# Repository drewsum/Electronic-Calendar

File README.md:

# Electronic-Calendar
Small PCB to show Time, Date, and Day of the Week. Centered around a PIC32MZ

Hardware:
KiCad Project for single PCB is located in hdw/KiCad_Project
Built in KiCad 5.1.0
Requires drewsum's custom libraries for KiCad schematic symbols and PCB footprints, located at: https://github.com/drewsum/KiCad_Custom_Libraries.git

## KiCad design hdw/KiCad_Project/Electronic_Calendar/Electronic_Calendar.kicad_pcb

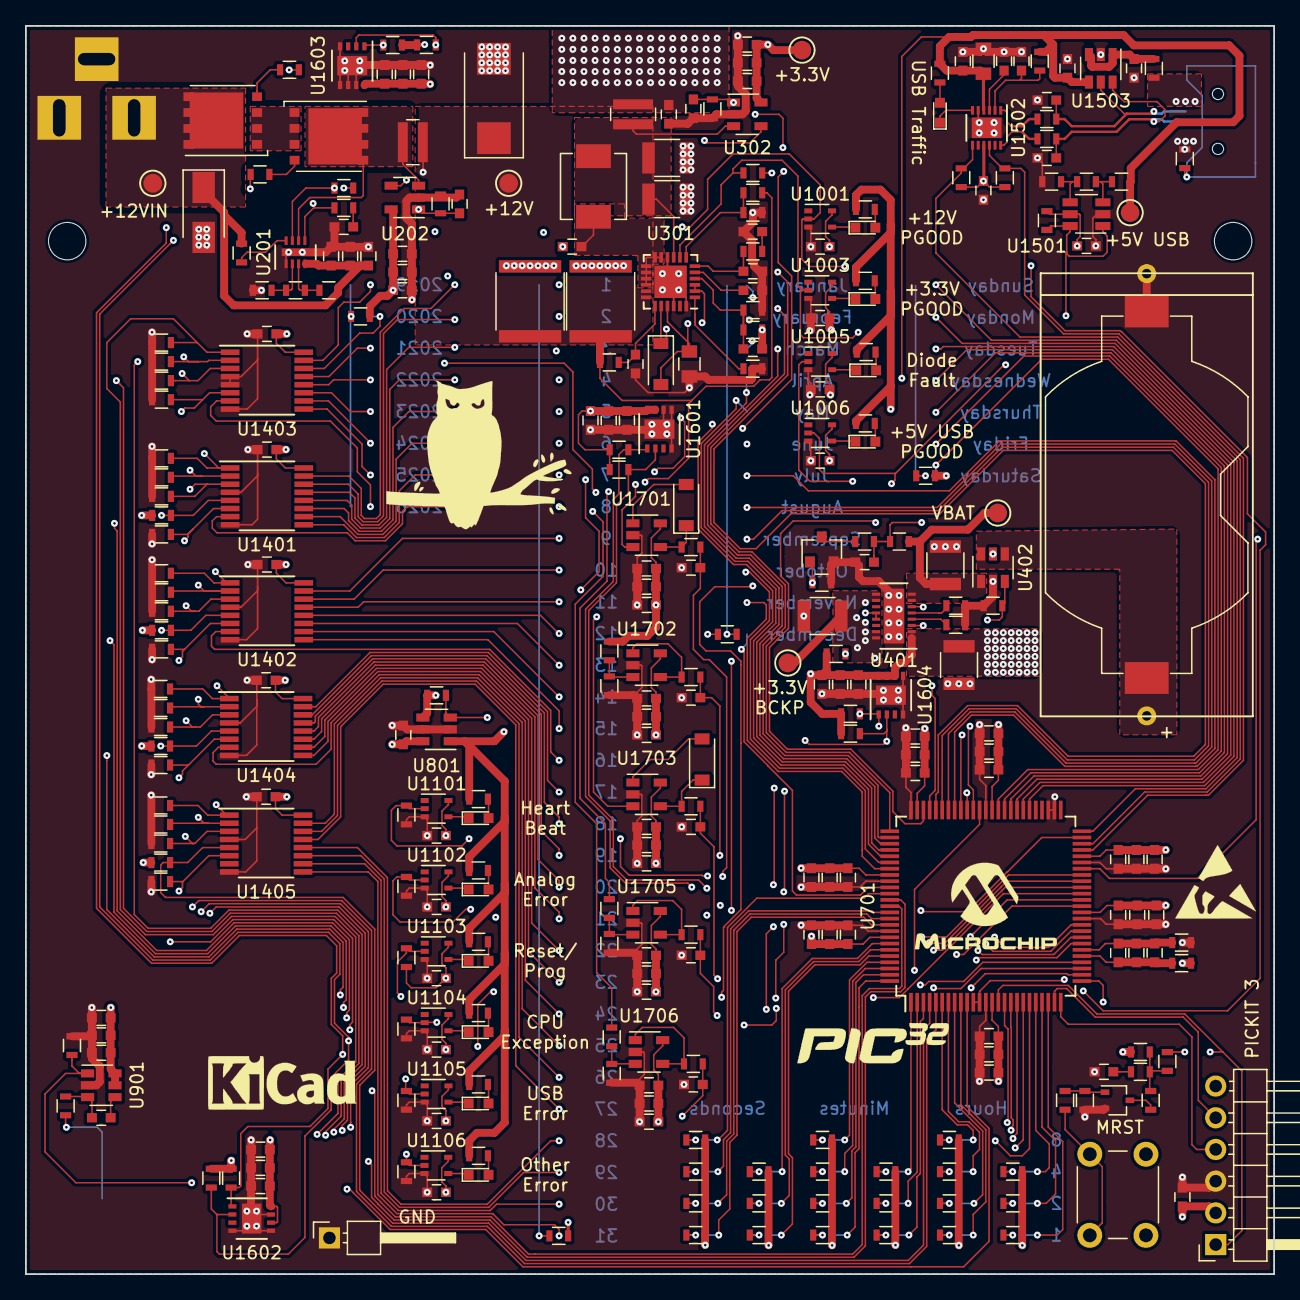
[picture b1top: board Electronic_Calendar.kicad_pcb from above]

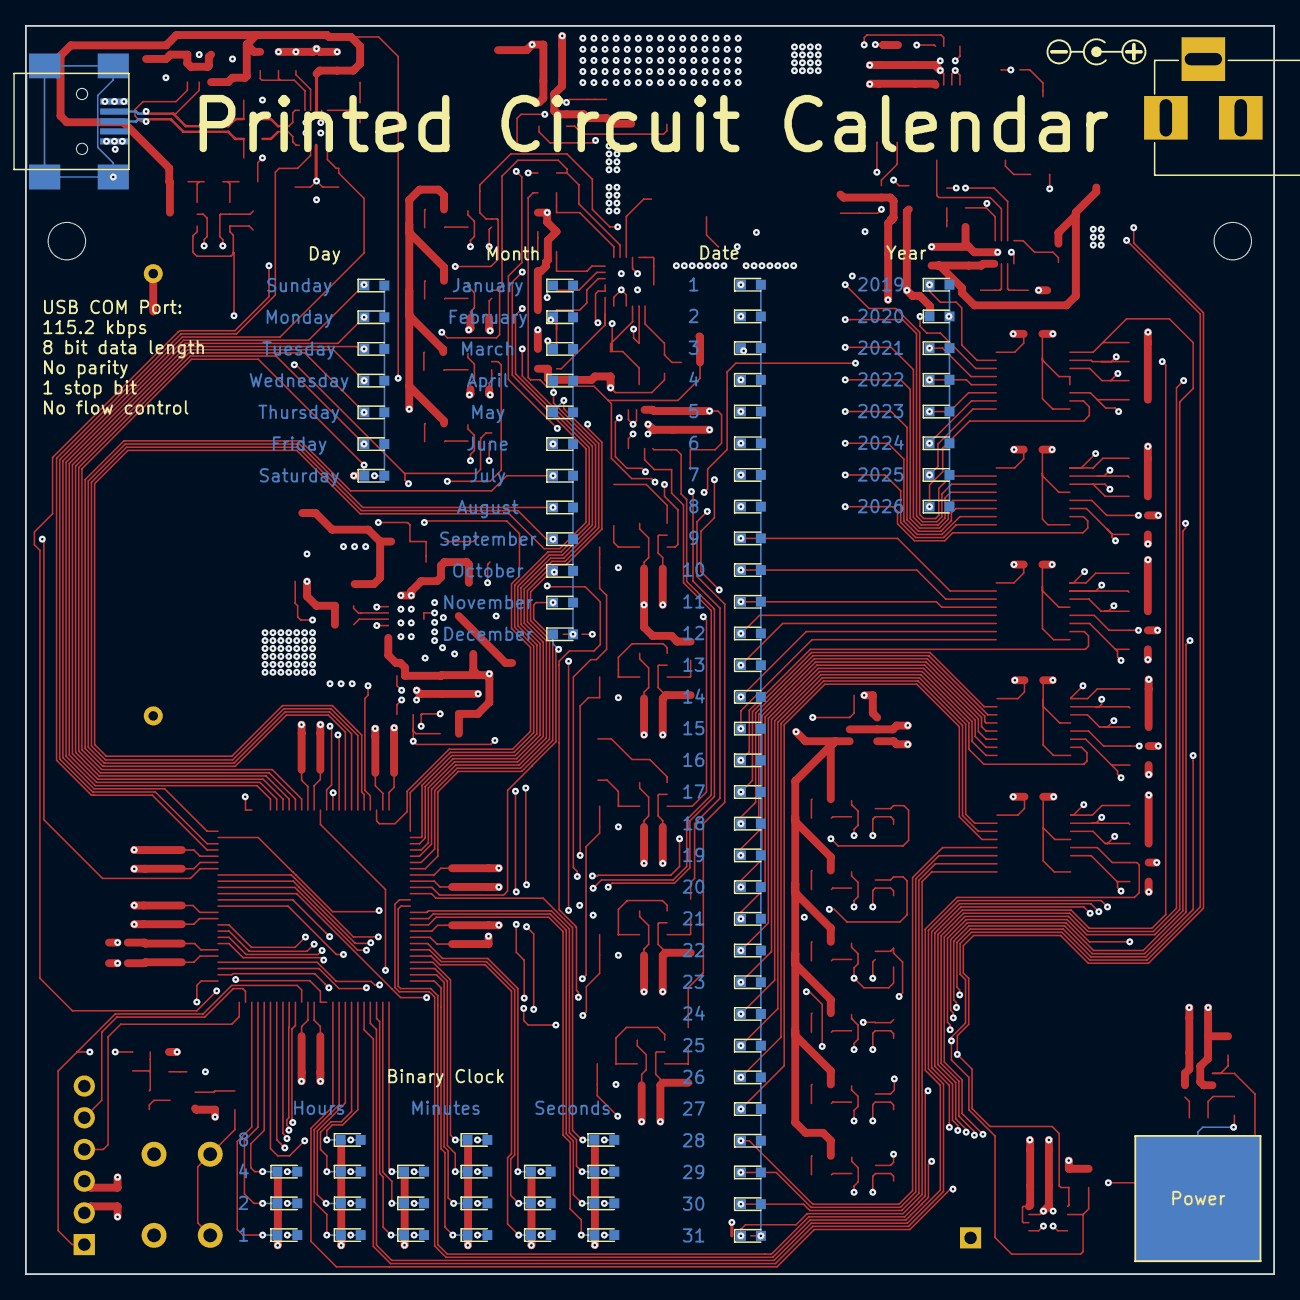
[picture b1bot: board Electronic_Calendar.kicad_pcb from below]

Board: 4 copper layers, 100.0 x 100.0 mm, 399 parts (82 on the bottom side), 229 nets.

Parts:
BT401: BR-2/3AE5SPN; BR-2_3AE5SPN
C201, C204, C205, C305, C307, C311, C316, C401, C601, C602, C801, C802, C807, C808, C813, C814, C819, C820, C825, C902, C1001, C1003, C1005, C1006, C1101, C1102, C1103, C1104, C1105, C1106, C1401, C1402, C1403, C1404, C1405, C1501, C1502, C1503, C1504, C1506, C1507, C1510, C1601, C1602, C1603, C1610, C1701, C1702, C1709, C1717, C1718: 0.1uF; C_0603
C202, C206, C304, C313, C803, C804, C809, C810, C815, C816, C821, C822, C901, C903, C1604, C1605, C1606, C1611, C1703, C1704, C1707, C1708, C1711, C1715, C1719, C1720, C1723, C1724: 10nF; C_0603
C203, C207, C208, C314, C317, C805, C806, C811, C812, C817, C818, C823, C824, C904, C1607, C1608, C1609, C1612, C1705, C1706, C1713, C1721, C1722: 1nF; C_0603
C209: 100uF; CP_Tantalum_Case-X_EIA-7343-43_Reflow
C301, C302: 22uF; C_2220
C306: 62pF; C_0603
C308, C310: 15pF; C_0603
C309: 2.2uF; C_0805
C312, C315, C402, C403, C404: 47uF; C_1210
C1505: 4.7uF; C_0805
C1508, C1509: 47pF; C_0603
D201: 24V; D_SMA
D301, D1601, D1602: MBR0530; D_SOD-123
D1001, D1003, D1006, D1101: Green; LED_0603
D1005, D1102, D1103, D1104, D1105, D1106, D1201, D1202, D1203, D1204, D1205, D1206, D1207, D1208, D1209, D1210, D1211, D1212, D1213, D1214, D1215, D1216, D1217, D1218, D1219, D1220, D1221, D1222, D1223, D1224, D1225, D1226, D1227, D1228, D1229, D1230, D1231, D1232, D1233, D1234, D1235, D1236, D1237, D1238, D1239, D1240, D1241, D1242, D1243, D1244, D1245, D1246, D1247, D1248, D1249, D1250, D1251, D1252, D1253, D1254, D1255, D1256, D1257, D1258, D1301, D1302, D1303, D1304, D1305, D1306, D1307, D1308, D1309, D1310, D1311, D1312, D1313, D1314, D1315, D1316, D1317, D1318, D1319, D1320, D1321: Red; LED_0603
D1501: Yellow; LED_0603
J201: +12V IN; BARREL_JACK
J601: PICKIT3; PICKIT3_Header
J1501: USB_B_Mini; USB_Mini-B
L301: 0.47uH; L_Vishay_IHLP-2020
L801, L802, L1501, L1502: 600R 0.5A; L_0603
Q201, Q202: IPC100N04S51R2ATMA1; TDSON-8-1
Q401: 2N7002; SOT-23
Q601: BSS214NW; SOT-323_SC-70
R201: 6.04M; R_0603
R202: 86.6k; R_0603
R203, R401, R402, R407: 243k; R_0603
R204, R302, R307, R310: 100k; R_0603
R205, R206, R304, R601: 10; R_0603
R207, R301, R403, R406, R602, R604, R801, R902, R1101, R1102, R1105, R1106, R1109, R1110, R1401, R1402, R1403, R1404, R1405, R1406, R1407, R1408, R1409, R1410, R1411, R1412, R1413, R1414, R1415, R1416, R1417, R1418, R1419, R1420, R1421, R1422, R1423, R1424, R1501, R1505, R1506, R1507, R1607, R1608, R1609, R1610, R1611, R1612, R1615, R1616, R1701, R1702, R1707, R1709, R1710: 10k; R_0603
R208: 5.1k; R_0603
R209, R309: 0.02; R_0612
R210: 249k; R_0603
R303, R308: 22.1k; R_0603
R305: 63.4k; R_0603
R306: 13.3k; R_0603
R404, R405, R901, R1703, R1704, R1705, R1711, R1712: 499; R_0603
R603: 100; R_0603
R605: 0; R_0603
R606, R1001, R1003, R1005, R1006, R1103, R1104, R1107, R1108, R1111, R1112, R1201, R1202, R1203, R1204, R1301, R1302, R1303, R1304, R1305, R1306, R1307, R1308, R1309, R1310, R1311, R1312, R1313, R1314, R1315, R1316, R1317, R1318, R1319, R1320, R1321, R1510: 1k; R_0603
R1502: 487k; R_0603
R1503: 6.04k; R_0603
R1504: 40.2k; R_0603
R1508, R1509: 27; R_0603
R1708: 1.2k; R_0603
SW601: MRST; SW_PUSH_6mm
SW901: Cap_Touch; Capacitive_Touch_Pad
TP201: TP; Pin_Header_Angled_1x01_Pitch2.54mm
TP203, TP204, TP301, TP401, TP402, TP1501: TP; Test_Point
U201: LTC4365DDB; DFN-8-1EP_2x3mm_Pitch0.5mm
U202, U302: INA138; SOT-23-5
U301: LTC3605A_UF; QFN-24-1EP_4x4mm_Pitch0.5mm
U401: LTC4415DHC; DFN-16-1EP_3x5mm_Pitch0.5mm
U402, U801: TPS22929D; SOT-23-6
U701: PIC32MZ2048EFG100_IPT; TQFP-100_14x14mm_Pitch0.5mm
U901: AT42QT1010-TSHR; SOT-23-6
U1001, U1003, U1006, U1101, U1102, U1103, U1104, U1105, U1106: 74LVC1G06; SOT-353_SC-70-5
U1005: 74LVC1G17; SOT-353_SC-70-5
U1401, U1402, U1403, U1404, U1405: 74HC138; TSSOP-16_4.4x5mm_Pitch0.65mm
U1501: LT6700-1-S6; TSOT-23-6
U1502: FT234XD; DFN-12-1EP_3x3mm_Pitch0.45mm
U1503: TPD3S014DBVR; SOT-23-6
U1601, U1602, U1603, U1604: MCP9804_DFN; DFN-8-1EP_3x3mm_Pitch0.65mm
U1701, U1702, U1703, U1705, U1706: OPA340NA; SOT-23-5

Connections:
+3.3VA: C820.1, C822.1, C824.1, L801.1, U701.30
+3.3V_BCKP: C404.1, C601.1, C801.1, C802.1, C803.1, C804.1, C805.1, C806.1, C807.1, C808.1, C809.1, C810.1, C811.1, C812.1, C813.1, C814.1, C815.1, C816.1, C817.1, C818.1, C819.1, C821.1, C823.1, J601.2, L801.2, R604.1, SW601.1, TP401.1, U401.9, U401.10, U401.15, U401.16, U701.14, U701.37, U701.46, U701.62, U701.74, U701.83, U701.93
+3.3V_STAT: R1001.1, R1003.1, R1005.1, R1006.1, R1103.1, R1104.1, R1107.1, R1108.1, R1111.1, R1112.1, U801.1
+3V3: C205.1, C206.1, C207.1, C310.1, C311.1, C313.1, C314.1, C316.1, C402.1, C825.1, C902.1, C903.1, C904.1, C1001.1, C1003.1, C1005.1, C1006.1, C1101.1, C1102.1, C1103.1, C1104.1, C1105.1, C1106.1, C1401.1, C1402.1, C1403.1, C1404.1, C1405.1, C1502.1, C1503.1, C1601.1, C1602.1, C1603.1, C1604.1, C1605.1, C1606.1, C1607.1, C1608.1, C1609.1, C1610.1, C1611.1, C1612.1, C1701.1, C1702.1, C1703.1, C1704.1, C1705.1, C1706.1, C1709.1, C1711.1, C1713.1, C1717.1, C1718.1, C1719.1, C1720.1, C1721.1, C1722.1, R207.1, R301.1, R307.1, R309.2, R406.1, R801.1, R1105.1, R1201.1, R1202.1, R1203.1, R1204.1, R1301.1, R1302.1, R1303.1, R1304.1, R1305.1, R1306.1, R1307.1, R1308.1, R1309.1, R1310.1, R1311.1, R1312.1, R1313.1, R1314.1, R1315.1, R1316.1, R1317.1, R1318.1, R1319.1, R1320.1, R1321.1, R1413.1, R1414.1, R1423.1, R1424.1, R1505.1, R1506.1, R1507.1, R1607.1, R1608.1, R1609.1, R1610.1, R1611.1, R1612.1, R1615.1, R1616.1, R1701.2, TP301.1, U202.5, U302.4, U302.5, U401.1, U401.2, U801.4, U801.6, U901.5, U901.6, U1001.5, U1003.5, U1005.5, U1006.5, U1101.5, U1102.5, U1103.5, U1104.5, U1105.5, U1106.5, U1401.16, U1402.16, U1403.16, U1404.16, U1405.16, U1501.5, U1502.9, U1601.7, U1601.8, U1602.6, U1602.8, U1603.8, U1604.6, U1604.7, U1604.8, U1701.5, U1702.5, U1703.5, U1705.5, U1706.5
+5V_USB: C1504.1, C1505.1, C1507.1, R1501.1, R1502.1, R1510.1, R1709.2, TP1501.1, U1502.4, U1503.4
+12V: C209.1, C301.1, C302.1, R209.2, R302.1, R304.1, R1707.2, TP204.1, U202.4, U301.17, U301.18
+12Vin: C201.1, C202.1, C203.1, D201.1, J201.1, Q201.5, R201.1, R204.1, TP203.1, U201.4
/USB UART Bridge/BRIDGE_USB+: R1508.2, U1502.12
/USB UART Bridge/BRIDGE_USB-: R1509.2, U1502.1
/USB UART Bridge/CONN_USB+: C1508.1, J1501.3, R1508.1, U1503.6
/USB UART Bridge/CONN_USB-: C1509.1, J1501.2, R1509.1, U1503.5
Analog_Error_LED: R1102.1, U701.34, U1102.2
Cap_Touch_Power: R902.1, U701.10, U901.1
Date_B0: R1401.1, R1402.1, R1415.1, R1416.1, U701.17, U1401.1, U1402.1, U1404.1, U1405.1
Date_B1: R1404.1, R1405.1, R1417.1, R1418.1, U701.16, U1401.2, U1402.2, U1404.2, U1405.2
Date_B2: R1407.1, R1408.1, R1419.1, R1420.1, U701.5, U1401.3, U1402.3, U1404.3, U1405.3
Date_Decode_Enable: R1410.1, R1411.1, R1412.1, R1421.1, R1422.1, U701.29, U1401.6, U1402.6, U1403.6, U1404.6, U1405.6
Exception_LED: R1106.1, U701.64, U1104.2
GND: BT401.2, C201.2, C202.2, C203.2, C204.2, C205.2, C206.2, C207.2, C208.2, C209.2, C301.2, C302.2, C304.2, C305.2, C306.2, C308.2, C309.2, C311.2, C312.2, C313.2, C314.2, C315.2, C316.2, C317.2, C401.2, C402.2, C403.2, C404.2, C601.2, C602.2, C801.2, C802.2, C803.2, C804.2, C805.2, C806.2, C807.2, C808.2, C809.2, C810.2, C811.2, C812.2, C813.2, C814.2, C815.2, C816.2, C817.2, C818.2, C819.2, C821.2, C823.2, C825.2, C902.2, C903.2, C904.2, C1001.2, C1003.2, C1005.2, C1006.2, C1101.2, C1102.2, C1103.2, C1104.2, C1105.2, C1106.2, C1401.2, C1402.2, C1403.2, C1404.2, C1405.2, C1501.2, C1502.2, C1503.2, C1504.2, C1505.2, C1506.2, C1507.2, C1508.2, C1509.2, C1510.2, C1601.2, C1602.2, C1603.2, C1604.2, C1605.2, C1606.2, C1607.2, C1608.2, C1609.2, C1610.2, C1611.2, C1612.2, C1701.2, C1702.2, C1703.2, C1704.2, C1705.2, C1706.2, C1707.2, C1708.2, C1709.2, C1711.2, C1713.2, C1715.2, C1717.2, C1718.2, C1719.2, C1720.2, C1721.2, C1722.2, C1723.2, C1724.2, D201.2, J201.2, J201.3, J601.3, J1501.5, L802.2, L1502.1, Q401.2, Q601.2, R203.2, R210.2, R303.2, R305.2, R308.2, R310.2, R403.2, R404.2, R405.2, R407.2, R602.2, R902.2, R1101.2, R1102.2, R1106.2, R1109.2, R1110.2, R1401.2, R1402.2, R1403.2, R1404.2, R1405.2, R1406.2, R1407.2, R1408.2, R1409.2, R1410.2, R1411.2, R1412.2, R1415.2, R1416.2, R1417.2, R1418.2, R1419.2, R1420.2, R1421.2, R1422.2, R1504.2, R1702.1, R1708.2, R1710.1, TP201.1, U201.1, U201.9, U202.2, U301.10, U301.22, U301.24, U301.25, U302.2, U401.17, U402.2, U402.5, U701.13, U701.36, U701.45, U701.52, U701.53, U701.63, U701.75, U701.84, U701.92, U801.2, U801.5, U901.2, U1001.3, U1003.3, U1005.3, U1006.3, U1101.3, U1102.3, U1103.3, U1104.3, U1105.3, U1106.3, U1401.4, U1401.8, U1402.4, U1402.8, U1403.4, U1403.5, U1403.8, U1404.4, U1404.8, U1405.4, U1405.8, U1501.2, U1502.5, U1502.13, U1503.2, U1601.4, U1601.5, U1601.6, U1601.9, U1602.4, U1602.5, U1602.7, U1602.9, U1603.4, U1603.5, U1603.6, U1603.7, U1603.9, U1604.4, U1604.5, U1604.9, U1701.2, U1702.2, U1703.2, U1705.2, U1706.2
GNDA: C820.2, C822.2, C824.2, L802.1, U701.31
Heartbeat_LED: R1101.1, U701.49, U1101.2
ICSPCLK: J601.5, U701.24
ICSPDAT: J601.4, U701.25
unnamed: BT401.1, U402.4, U402.6
unnamed: C204.1, R208.2
unnamed: C304.1, U301.5
unnamed: C305.1, R304.2, U301.19
unnamed: C306.1, R306.2
unnamed: C307.1, D301.1, U301.20
unnamed: C307.2, L301.1, U301.11, U301.12, U301.13, U301.14, U301.15, U301.16
unnamed: C308.1, R306.1, U301.6
unnamed: C309.1, D301.2, U301.2, U301.3, U301.21
unnamed: C310.2, R307.2, R308.1, U301.4
unnamed: C312.1, C315.1, L301.2, R309.1, U301.9, U302.3
unnamed: C602.1, R605.2
unnamed: C901.1, U901.4
unnamed: C901.2, R901.2, U901.3
unnamed: C1501.1, R1501.2, U1502.2
unnamed: C1506.1, U1502.3
unnamed: C1510.1, L1501.2, U1503.1, U1503.3
unnamed: D1001.1, U1001.4
unnamed: D1001.2, R1001.2
unnamed: D1003.1, U1003.4
unnamed: D1003.2, R1003.2
unnamed: D1005.1, U1005.4
unnamed: D1005.2, R1005.2
unnamed: D1006.1, U1006.4
unnamed: D1006.2, R1006.2
unnamed: D1101.1, U1101.4
unnamed: D1101.2, R1103.2
unnamed: D1102.1, U1102.4
unnamed: D1102.2, R1104.2
unnamed: D1103.1, U1103.4
unnamed: D1103.2, R1107.2
unnamed: D1104.1, U1104.4
unnamed: D1104.2, R1108.2
unnamed: D1105.1, U1105.4
unnamed: D1105.2, R1111.2
unnamed: D1106.1, U1106.4
unnamed: D1106.2, R1112.2
unnamed: D1201.2, D1202.2, D1203.2, D1204.2, D1205.2, D1206.2, D1207.2, D1208.2, D1209.2, D1210.2, D1211.2, D1212.2, R1201.2
unnamed: D1213.2, D1214.2, D1215.2, D1216.2, D1217.2, D1218.2, D1219.2, D1220.2, D1221.2, D1222.2, D1223.2, D1224.2, D1225.2, D1226.2, D1227.2, D1228.2, D1236.2, D1237.2, D1238.2, D1239.2, D1240.2, D1241.2, D1242.2, D1243.2, D1244.2, D1245.2, D1246.2, D1247.2, D1248.2, D1249.2, D1250.2, R1202.2
unnamed: D1229.2, D1230.2, D1231.2, D1251.2, D1252.2, D1253.2, D1254.2, R1203.2
unnamed: D1232.2, D1233.2, D1234.2, D1235.2, D1255.2, D1256.2, D1257.2, D1258.2, R1204.2
unnamed: D1301.2, R1301.2
unnamed: D1302.2, R1302.2
unnamed: D1303.2, R1303.2
unnamed: D1304.2, R1304.2
unnamed: D1305.2, R1305.2
unnamed: D1306.2, R1306.2
unnamed: D1307.2, R1307.2
unnamed: D1308.2, R1308.2
unnamed: D1309.2, R1309.2
unnamed: D1310.2, R1310.2
unnamed: D1311.2, R1311.2
unnamed: D1312.2, R1312.2
unnamed: D1313.2, R1313.2
unnamed: D1314.2, R1314.2
unnamed: D1315.2, R1315.2
unnamed: D1316.2, R1316.2
unnamed: D1317.2, R1317.2
unnamed: D1318.2, R1318.2
unnamed: D1319.2, R1319.2
unnamed: D1320.2, R1320.2
unnamed: D1321.2, R1321.2
unnamed: D1501.2, R1510.2
unnamed: D1601.1, R1703.2, U1701.4
unnamed: D1601.2, U1701.1
unnamed: D1602.1, R1705.2, U1703.4
unnamed: D1602.2, U1703.1
unnamed: J1501.1, L1501.1
unnamed: J1501.6, L1502.2
unnamed: Q201.1, Q201.2, Q201.3, Q202.1, Q202.2, Q202.3
unnamed: Q201.4, R205.2
unnamed: Q202.4, R206.1
unnamed: Q202.5, R209.1, U201.6, U202.3
unnamed: Q401.3, R402.2
unnamed: Q601.1, R601.2, R602.1
unnamed: Q601.3, R603.2
unnamed: R201.2, R202.1, U201.3
unnamed: R202.2, R203.1, U201.2
unnamed: R204.2, U201.8
unnamed: R205.1, R206.2, R208.1, U201.5
unnamed: R302.2, R303.1, U301.7
unnamed: R305.1, U301.1
unnamed: R404.1, U401.4
unnamed: R405.1, U401.5
unnamed: R601.1, SW601.2
unnamed: R603.1, R604.2, R605.1, R606.2
unnamed: R901.1, SW901.1
unnamed: R1502.2, R1503.1, U1501.3
unnamed: R1503.2, R1504.1, U1501.4
unnamed: R1701.1, R1702.2, U1702.3
unnamed: R1704.2, U1702.1, U1702.4
unnamed: R1707.1, R1708.1, U1705.3
unnamed: R1709.1, R1710.2, U1706.3
unnamed: R1711.2, U1705.1, U1705.4
unnamed: R1712.2, U1706.1, U1706.4
Other_Error_LED: R1110.1, U701.87, U1106.2
POS3P3_ADC: C1708.1, R1704.1, U701.32
POS3P3_ISNS: C317.1, R310.1, U302.1, U1703.3
POS3P3_ISNS_ADC: C1715.1, R1705.1, U701.38
POS3P3_PGOOD: R301.2, U301.8, U401.3, U401.6, U701.72, U1003.2
POS5_USB_ADC: C1724.1, R1712.1, U701.26
POS5_USB_PGOOD: R1507.2, U701.73, U1006.2, U1501.1, U1501.6
POS12_ADC: C1723.1, R1711.1, U701.27
POS12_ISNS: C208.1, R210.1, U202.1, U1701.3
POS12_ISNS_ADC: C1707.1, R1703.1, U701.33
POS12_PGOOD: R207.2, U201.7, U701.11, U701.12, U1001.2
Reset_LED: R1105.2, U701.28, U1103.2
STATUS_LED_ENABLE: R801.2, U701.35, U801.3
TEMP_I2C_SCL: R1610.2, R1611.2, R1612.2, R1616.2, U701.66, U1601.2, U1602.2, U1603.2, U1604.2
TEMP_I2C_SDA: R1607.2, R1608.2, R1609.2, R1615.2, U701.67, U1601.1, U1602.1, U1603.1, U1604.1
USB_Error_LED: R1109.1, U701.88, U1105.2
USB_UART_RX: R1506.2, U701.48, U1502.7
USB_UART_TX: R1505.2, U701.47, U1502.10
VBAT: C403.1, R401.1, TP402.1, U401.7, U401.8, U402.1
VBAT_ADC: C401.1, R401.2, R402.1, U701.44
VBAT_ADC_EN: Q401.1, R403.1, U701.40
Year_B0: R1403.1, U701.20, U1403.1
Year_B1: R1406.1, U701.18, U1403.2
Year_B2: R1409.1, U701.19, U1403.3
~APR_LED: D1208.1, U701.78
~AUG_LED: D1210.1, U701.69
~DEC_LED: D1212.1, U701.85
~DIODE_FAULT: R406.2, U401.12, U401.13, U701.39, U1005.2
~Date1_LED: D1213.1, U1401.15
~Date2_LED: D1236.1, U1401.14
~Date3_LED: D1214.1, U1401.13
~Date4_LED: D1237.1, U1401.12
~Date5_LED: D1215.1, U1401.11
~Date6_LED: D1238.1, U1401.10
~Date7_LED: D1216.1, U1401.9
~Date8_LED: D1239.1, U1401.7
~Date9_LED: D1217.1, U1402.15
~Date10_LED: D1240.1, U1402.14
~Date11_LED: D1218.1, U1402.13
~Date12_LED: D1241.1, U1402.12
~Date13_LED: D1219.1, U1402.11
~Date14_LED: D1242.1, U1402.10
~Date15_LED: D1220.1, U1402.9
~Date16_LED: D1243.1, U1402.7
~Date17_LED: D1221.1, U1404.15
~Date18_LED: D1244.1, U1404.14
~Date19_LED: D1222.1, U1404.13
~Date20_LED: D1245.1, U1404.12
~Date21_LED: D1223.1, U1404.11
~Date22_LED: D1246.1, U1404.10
~Date23_LED: D1224.1, U1404.9
~Date24_LED: D1247.1, U1404.7
~Date25_LED: D1225.1, U1405.15
~Date26_LED: D1248.1, U1405.14
~Date27_LED: D1226.1, U1405.13
~Date28_LED: D1249.1, U1405.12
~Date29_LED: D1227.1, U1405.11
~Date30_LED: D1250.1, U1405.10
~Date31_LED: D1228.1, U1405.9
~Date_Decode_1: R1413.2, U701.41, U1401.5
~Date_Decode_2: R1414.2, U701.42, U1402.5
~Date_Decode_3: R1423.2, U701.43, U1404.5
~Date_Decode_4: R1424.2, U701.4, U1405.5
~FEB_LED: D1207.1, U701.76
~FRI_LED: D1231.1, U701.60
~Hours0_LED: D1301.1, U701.6
~Hours1_LED: D1313.1, U701.21
~Hours2_LED: D1302.1, U701.7
~Hours3_LED: D1314.1, U701.22
~Hours4_LED: D1303.1, U701.8
~Hours5_LED: D1315.1, U701.23
~Hours6_LED: D1304.1, U701.9
~JAN_LED: D1201.1, U701.71
~JUL_LED: D1204.1, U701.68
~JUN_LED: D1209.1, U701.80
~MAR_LED: D1202.1, U701.77
~MAY_LED: D1203.1, U701.79
~MCLR: J601.1, R606.1, U701.15
~MON_LED: D1229.1, U701.56
~Minutes0_LED: D1305.1, U701.97
~Minutes1_LED: D1316.1, U701.1
~Minutes2_LED: D1306.1, U701.98
~Minutes3_LED: D1317.1, U701.2
~Minutes4_LED: D1307.1, U701.99
~Minutes5_LED: D1318.1, U701.3
~Minutes6_LED: D1308.1, U701.100
~NOV_LED: D1206.1, U701.82
~OCT_LED: D1211.1, U701.81
~SAT_LED: D1254.1, U701.61
~SEP_LED: D1205.1, U701.70
~SUN_LED: D1251.1, U701.50
~Seconds0_LED: D1309.1, U701.86
~Seconds1_LED: D1319.1, U701.94
~Seconds2_LED: D1310.1, U701.89
~Seconds3_LED: D1320.1, U701.95
~Seconds4_LED: D1311.1, U701.90
~Seconds5_LED: D1321.1, U701.96
~Seconds6_LED: D1312.1, U701.91
~THR_LED: D1253.1, U701.59
~TUE_LED: D1252.1, U701.57
~USB_TRAFFIC: D1501.1, U1502.6
~VBAT_ISOLATE: R407.1, U402.3, U701.65
~WED_LED: D1230.1, U701.58
~Year2019_LED: D1232.1, U1403.15
~Year2020_LED: D1255.1, U1403.14
~Year2021_LED: D1233.1, U1403.13
~Year2022_LED: D1256.1, U1403.12
~Year2023_LED: D1234.1, U1403.11
~Year2024_LED: D1257.1, U1403.10
~Year2025_LED: D1235.1, U1403.9
~Year2026_LED: D1258.1, U1403.7

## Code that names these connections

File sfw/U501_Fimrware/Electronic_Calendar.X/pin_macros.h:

/* ************************************************************************** */
/** Descriptive File Name

  @Company
    Company Name

  @File Name
    filename.h

  @Summary
    Brief description of the file.

  @Description
    Describe the purpose of this file.
 */
/* ************************************************************************** */

#ifndef _PIN_MACROS_H    /* Guard against multiple inclusion */
#define _PIN_MACROS_H

#include <xc.h>

// These pin macros allow for easier manipulation of GPIO with matching
// signal names from the hardware schematic

// Port A
#define DATE_B0_PIN                 LATAbits.LATA0
#define nTHUR_LED_PIN               LATAbits.LATA2
#define nFRI_LED_PIN                LATAbits.LATA3
#define nSAT_LED_PIN                LATAbits.LATA4
#define nMINUTES3_PIN               LATAbits.LATA5
#define nSECONDS2_PIN               LATAbits.LATA6
#define nSECONDS4_PIN               LATAbits.LATA7
#define RESET_LED_PIN               LATAbits.LATA9
#define DATE_DECODE_ENABLE_PIN      LATAbits.LATA10

// Port B
#define nHOURS5_LED_PIN             LATBbits.LATB2
#define nHOURS3_LED_PIN             LATBbits.LATB3
#define nHOURS1_LED_PIN             LATBbits.LATB4
#define YEAR_B0_PIN                 LATBbits.LATB5
#define ANALOG_ERROR_LED_PIN        LATBbits.LATB10
#define STATUS_LED_ENABLE_PIN       LATBbits.LATB11
#define nDATE_DECODE_1_PIN          LATBbits.LATB12
#define nDATE_DECODE_2_PIN          LATBbits.LATB13
#define nDATE_DECODE_3_PIN          LATBbits.LATB14

// Port C
#define nHOURS0_LED_PIN             LATCbits.LATC1
#define nHOURS2_LED_PIN             LATCbits.LATC2
#define nHOURS4_LED_PIN             LATCbits.LATC3
#define nHOURS6_LED_PIN             LATCbits.LATC4
#define HEARTBEAT_LED_PIN           LATCbits.LATC12
#define POS3P3_PGOOD_PIN            PORTCbits.RC13
#define POS5_USB_PGOOD_PIN          PORTCbits.RC14
#define nSUN_LED_PIN                LATCbits.LATC15

// Port D
#define nJAN_LED_PIN                LATDbits.LATD0
#define nFEB_LED_PIN                LATDbits.LATD1
#define nMAR_LED_PIN                LATDbits.LATD2
#define nAPR_LED_PIN                LATDbits.LATD3
#define nOCT_LED_PIN                LATDbits.LATD4
#define nNOV_LED_PIN                LATDbits.LATD5
#define nJUL_LED_PIN                LATDbits.LATD9
#define nAUG_LED_PIN                LATDbits.LATD10
#define nSEP_LED_PIN                LATDbits.LATD11
#define nMAY_LED_PIN                LATDbits.LATD12
#define nJUN_LED_PIN                LATDbits.LATD13

// Port E
#define nSECONDS6_LED_PIN           LATEbits.LATE0
#define nSECONDS1_LED_PIN           LATEbits.LATE1
#define nMINUTES2_LED_PIN           LATEbits.LATE2
#define nMINUTES4_LED_PIN           LATEbits.LATE3
#define nMINUTES6_LED_PIN           LATEbits.LATE4
#define nMINUTED5_LED_PIN           LATEbits.LATE5
#define nDATE_DECODE_4_PIN          LATEbits.LATE6
#define DATE_B2_PIN                 LATEbits.LATE7
#define YEAR_B1_PIN                 LATEbits.LATE8
#define YEAR_B2_PIN                 LATEbits.LATE6

// Port F
#define nDEC_LED_PIN                LATFbits.LATF0
#define nSECONDS0_LED_PIN           LATFbits.LATF1
#define nTUE_LED_PIN                LATFbits.LATF2
#define nMON_LED_PIN                LATFbits.LATF3
#define EXCEPTION_LED_PIN           LATFbits.LATF4
#define nVBAT_ISOLATE_PIN           LATFbits.LATF5
#define nWED_LED_PIN                LATFbits.LATF8
#define VBAT_ADC_ENABLE_PIN         LATFbits.LATF12
#define nDIODE_FAULT_PIN            PORTFbits.RF13

// Port G
#define USB_ERROR_LED_PIN           LATGbits.LATG0
#define OTHER_ERROR_LED_PIN         LATGbits.LATG1
#define CAP_TOUCH_POWER_PIN         PORTGbits.RG6
#define POS12_PGOOD_PIN             PORTGbits.RG7
#define DATE_B1_PIN                 LATGbits.LATG9
#define nSECONDS5_LED_PIN           LATGbits.LATG12
#define nMINUTES0_LED_PIN           LATGbits.LATG13
#define nSECONDS3_LED_PIN           LATGbits.LATG14
#define nMINUTES1_LED_PIN           LATGbits.LATG15

#endif /* _PIN_MACROS_H */

/* *****************************************************************************
 End of File
 */

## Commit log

2019-05-09 Added KiCad files, started developing hardware
2019-05-09 Added temp sensors, other stuff
2019-06-20 Extensive LED drive restructuring
2019-07-17 Designed better date decoding
2019-07-20 Added software project, ported old code
2019-07-21 Schematic adjustments, PN assignments, footprints
2019-07-30 Begn laying out PCB
2019-07-31 Arranged a few more PCB sections
2019-08-06 More PCB part placement
2019-08-07 More part arranging on PCB
2019-08-07 even more arranging
2019-08-07 Finished grouping parts on PCB
2019-08-08 Decided on shape and placed sections onto PCB
2019-08-12 Began routing
2019-08-13 More routing
2019-08-15 Way more routing
2019-08-15 Even more routing
2019-08-27 Finished routing
2019-09-22 Updated PDF, BOM, Gerbers
2019-09-22 Added pin macros to firmware project
2019-09-22 Setup PLL for 200MHz SYSCLK
2019-09-22 Added GPIO init functions
2019-09-24 Edited error handler
2019-09-26 git ignoring LTSpice raw
2019-09-26 Added 3605 LTSpice sim
2019-10-03 Got heartbeat functionality working
2019-10-06 Got ring buffer based USB UART working
2019-10-07 Got basic DMA uart working, buffer still doesn't work
2019-10-08 Got DMA based USB UART transmit working
2019-10-08 Renamed firmware directory, added peripheral and interrupt spreadsheets
2019-10-09 Got DMA based USB UART RX working
2019-10-09 USB UART DMA refinements
2019-10-09 Added cause of reset detection
2019-10-09 Added PMD settings
2019-10-10 Got RTCC working, serial commands to set time and date
2019-10-11 Got a lot of calendar LEDs working
2019-10-13 Added isolation between usb uart tx and rx
2019-10-13 Added day LED driving stuff
2019-10-14 Got ADC7 working
2019-10-17 changed to combine both custom string comparison functions into one
2019-10-17 converted a few serial commands to new implementation
2019-10-17 added way more efficient custom string comparison
2019-10-18 Converted usb uart LUT to hash table based implementation
2019-10-18 Removed extra U3STA register write in main();
2019-10-22 Added more USB UART commands to hash table
2019-10-22 USB UART bug fixes
2019-10-24 Got ADC working
2019-10-25 Fixed strange ADC conversion issues. Had to slow down sampling speed.
2019-10-29 Added telemetry
2019-10-30 Added telemetry tracking, min and max telemetry, fixed underscore serial text, refactored ADC code, changed config words to disable WDT and DMT at boot
2019-10-30 Added functionality to set RTCC from 32 bit unix time
2019-10-30 a few cleanups
2019-11-02 Refactored error handling to be loopable
2019-11-02 Made error handler a persistent data type
2019-11-02 Error handler fixes, optimized ADC timing
2019-11-03 Got MCP9804 I2C temp sensors working
2019-11-05 USB UART in weird state
2019-11-05 DMT fixes
2019-11-06 Few tweaks, trying to fix WDT timeouts
2019-11-06 A few tweaks for optimization
2019-11-06 More tweaks
2019-11-07 Still in weird state, few optimizations
2019-11-09 I2C in weird state
2019-11-10 Starting over with firmware
2019-11-10 gitignore edits
2019-11-10 restarted fmw project
2019-11-11 got old project working again, ditched new project
2019-11-11 Changed REFCLK PMD setting to enabled per device errata
2019-11-11 Made a ton of variables volatile
2019-11-11 some cleanups
2019-11-11 made a few more variable volatile
2019-11-12 fixes to ADC code to resolve random CPU exceptions
2019-11-12 fixed ADC exception issues
2019-11-12 i2c tweaks
2019-11-13 Seems like I2C temp sensors are now working
2019-11-13 Switched to I2C non-blocking implementation, it works!
2019-11-13 Added power cap touch ISRs
2019-11-14 Added pushbutton IDLE mode control functions
2019-11-16 optimized USB UART RX string check further
2019-11-16 Made error handler __attribute__((persistent))
2019-11-17 Few tweaks on error handler and I2C
2019-11-17 added clock switch
2019-12-05 Added clock drift compensation to rtcc stuff
2020-01-11 Removed DMT clear stuff from heartbeat
2020-01-12 Tweaked firmware, added calibrate python script
2020-01-22 Few stability tweaks
2020-01-24 More stability improvement attempts
